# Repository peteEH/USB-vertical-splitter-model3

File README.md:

# USB-vertical-splitter-model3
Vertical USB Splitter - side firing receptacles

## LICENSE ##
Hardware License is Creative Commons - Attribution 3.0

Feel free to use these files to learn, explore electronics.

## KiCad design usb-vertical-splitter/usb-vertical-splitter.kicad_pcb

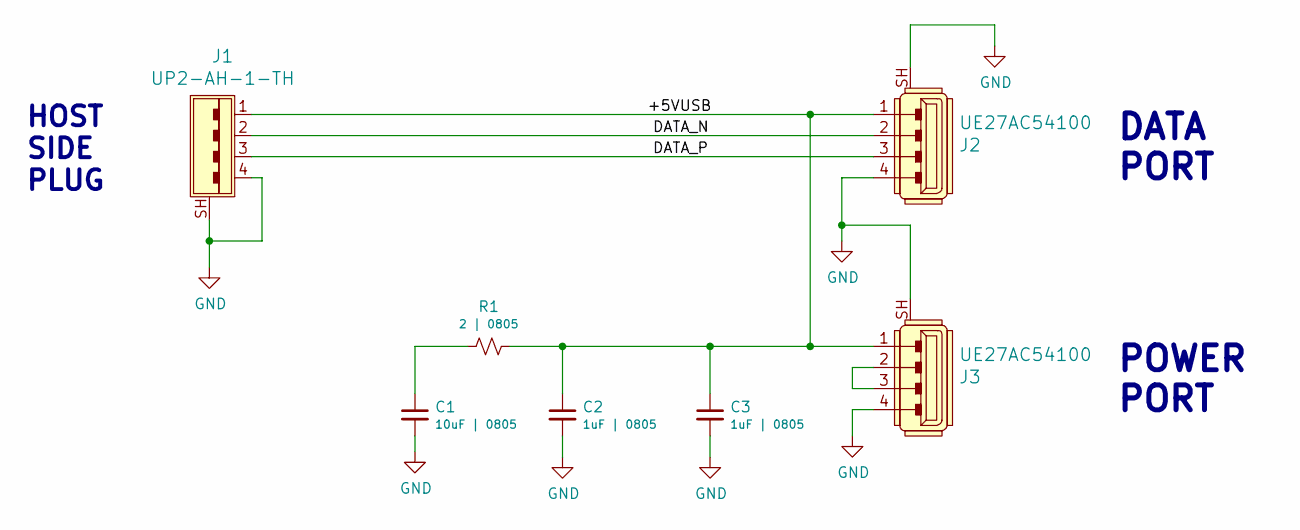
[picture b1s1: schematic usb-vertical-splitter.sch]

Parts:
C1: 10uF | 0805; C_0805_2012Metric
C2, C3: 1uF | 0805; C_0805_2012Metric
J1: UP2-AH-1-TH; USB_Male_A_UP2-AH-1-TH; MPN UP2-AH-1-TH; Digi-Key_PN 102-3996-ND
J2, J3: UE27AC54100; USB_A_Female_UE27AC54100; MPN UE27AC54100; Digi-Key_PN UE27AC54100-ND
R1: 2 | 0805; R_0805_2012Metric

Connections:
/+5VUSB: C2.1, C3.1, J1.1, J2.1, J3.1, R1.1
/DATA_N: J1.2, J2.2
/DATA_P: J1.3, J2.3
GND: C1.2, C2.2, C3.2, J1.4, J1.SH, J2.4, J2.SH, J3.4, J3.SH
unnamed: C1.1, R1.2
unnamed: J3.2, J3.3

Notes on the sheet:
POWER PORT
DATA PORT
HOST SIDE PLUG

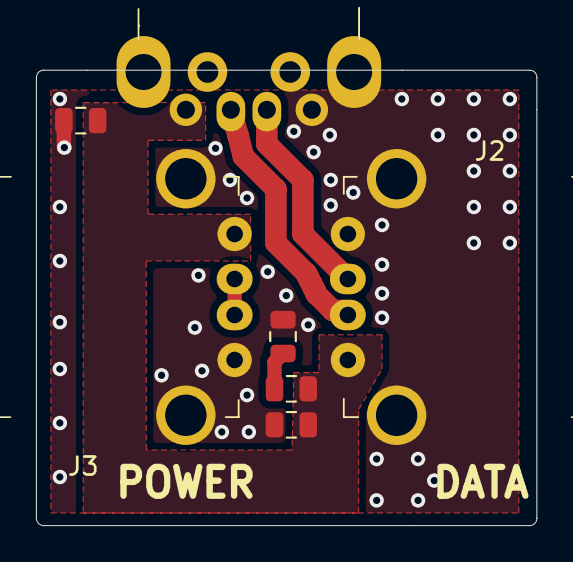
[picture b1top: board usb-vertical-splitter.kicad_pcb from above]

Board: 2 copper layers, 27.8 x 25.3 mm, 7 parts (0 on the bottom side), 6 nets.

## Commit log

2019-10-26 initial set of files
2019-10-26 added license
